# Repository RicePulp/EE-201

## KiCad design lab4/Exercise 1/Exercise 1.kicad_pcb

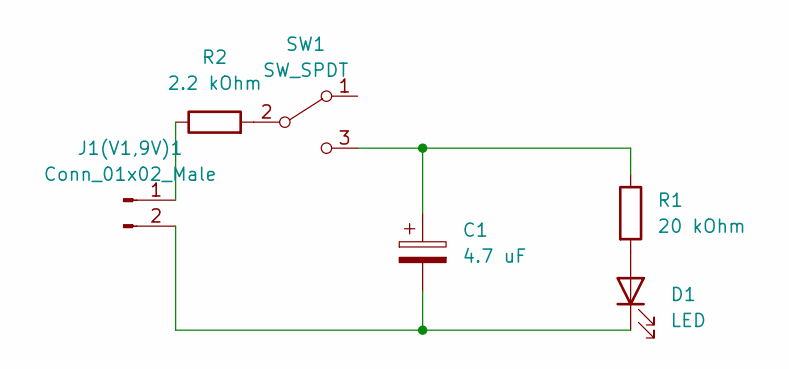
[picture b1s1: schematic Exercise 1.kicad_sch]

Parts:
C1: 4.7 uF; C_Radial_D5.0mm_H5.0mm_P2.00mm
D1: LED; LED_D5.0mm
J1(V1,9V)1: Conn_01x02_Male; JST_PH_B2B-PH-K_1x02_P2.00mm_Vertical
R1: 20 kOhm; R_Axial_DIN0516_L15.5mm_D5.0mm_P20.32mm_Horizontal
R2: 2.2 kOhm; R_Axial_DIN0516_L15.5mm_D5.0mm_P20.32mm_Horizontal
SW1: SW_SPDT; SW_E-Switch_EG1224_SPDT_Angled

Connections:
unnamed: C1.1, R1.1, SW1.3 (C)
unnamed: C1.2, D1.1 (K), J1(V1,9V)1.2
unnamed: J1(V1,9V)1.1, R2.1
unnamed: D1.2 (A), R1.2
unnamed: R2.2, SW1.2 (B)

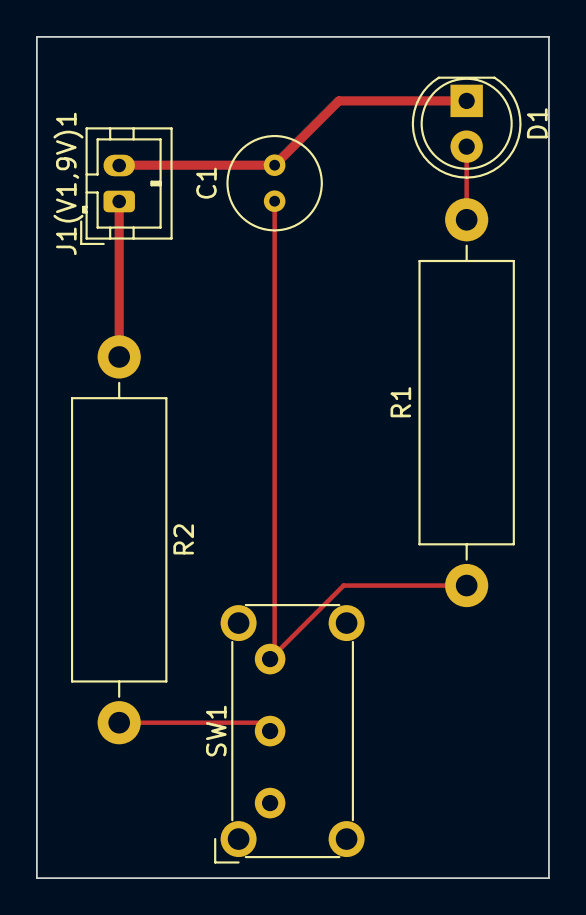
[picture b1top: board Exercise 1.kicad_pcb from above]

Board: 2 copper layers, 28.4 x 46.7 mm, 6 parts (0 on the bottom side), 5 nets.

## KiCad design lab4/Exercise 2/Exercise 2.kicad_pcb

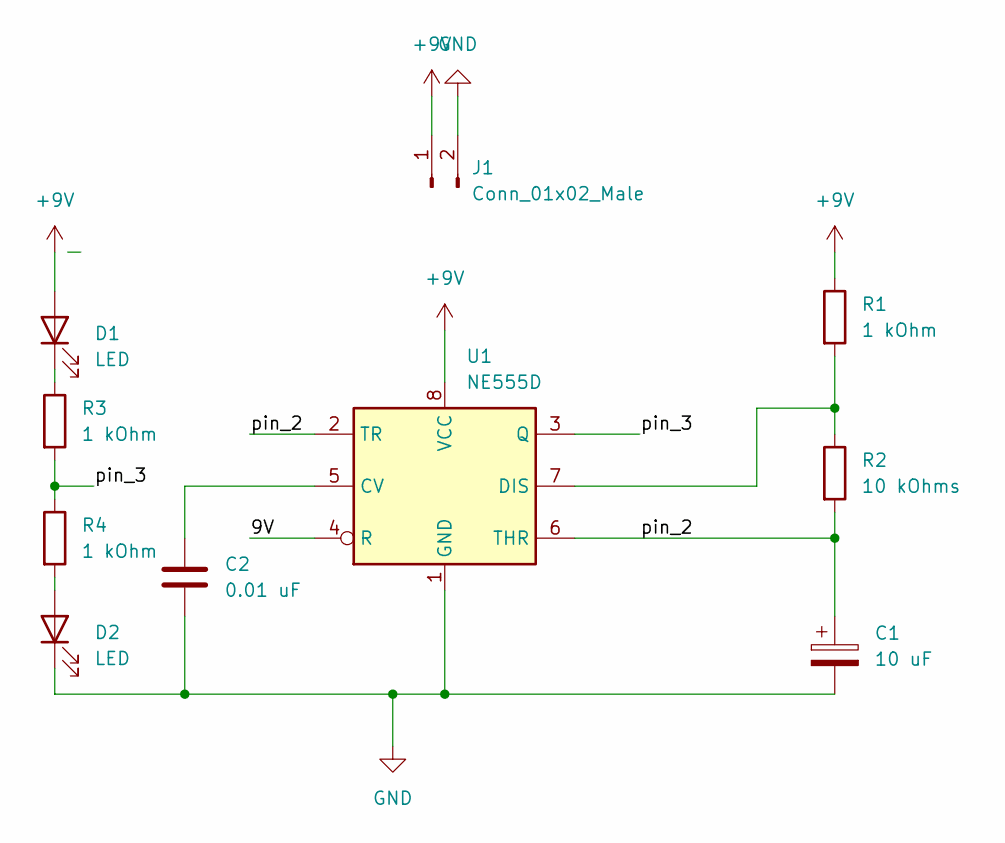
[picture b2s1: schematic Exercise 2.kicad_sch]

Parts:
C1: 10 uF; CP_EIA-3216-18_Kemet-A_Pad1.58x1.35mm_HandSolder
C2: 0.01 uF; C_0805_2012Metric_Pad1.18x1.45mm_HandSolder
D1, D2: LED; LED_1206_3216Metric_Pad1.42x1.75mm_HandSolder
J1: Conn_01x02_Male; TerminalBlock_bornier-2_P5.08mm
R1, R3, R4: 1 kOhm; R_0805_2012Metric_Pad1.20x1.40mm_HandSolder
R2: 10 kOhms; R_0805_2012Metric_Pad1.20x1.40mm_HandSolder
U1: NE555D; SOIC-8-1EP_3.9x4.9mm_P1.27mm_EP2.29x3mm

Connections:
+9V: D1.2 (A), J1.1, R1.1, U1.8 (VCC)
/9V: U1.4 (R)
/pin_2: C1.1, R2.2, U1.2 (TR), U1.6 (THR)
/pin_3: R3.2, R4.1, U1.3 (Q)
GND: C1.2, C2.2, D2.1 (K), J1.2, U1.1 (GND)
unnamed: C2.1, U1.5 (CV)
unnamed: D1.1 (K), R3.1
unnamed: D2.2 (A), R4.2
unnamed: R1.2, R2.1, U1.7 (DIS)

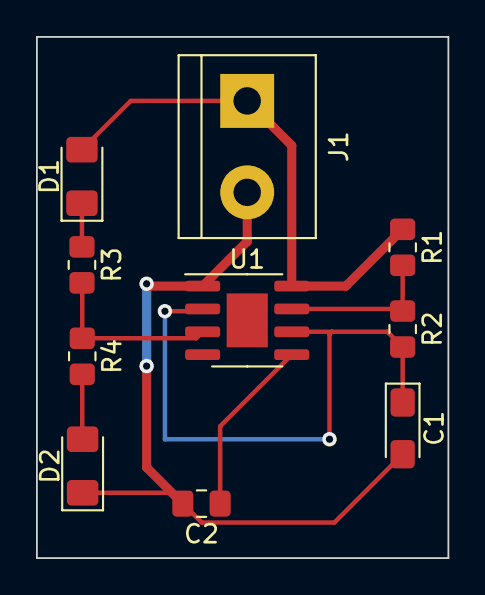
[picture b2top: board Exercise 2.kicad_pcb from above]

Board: 2 copper layers, 22.9 x 29.0 mm, 10 parts (0 on the bottom side), 8 nets.

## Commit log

2023-01-12 added aboutMe
2023-01-12 added img
2023-01-24 added arduino lab ex
2023-01-26 added lab 4 ex
2023-02-02 added soldering
2023-02-09 added PCB of the SCH
2023-02-14 added a clip
2023-02-14 deleted twitch
2023-02-16 added PCB gerber
2023-02-23 images of Arduometer solder
2023-03-09 finished arduometer build
